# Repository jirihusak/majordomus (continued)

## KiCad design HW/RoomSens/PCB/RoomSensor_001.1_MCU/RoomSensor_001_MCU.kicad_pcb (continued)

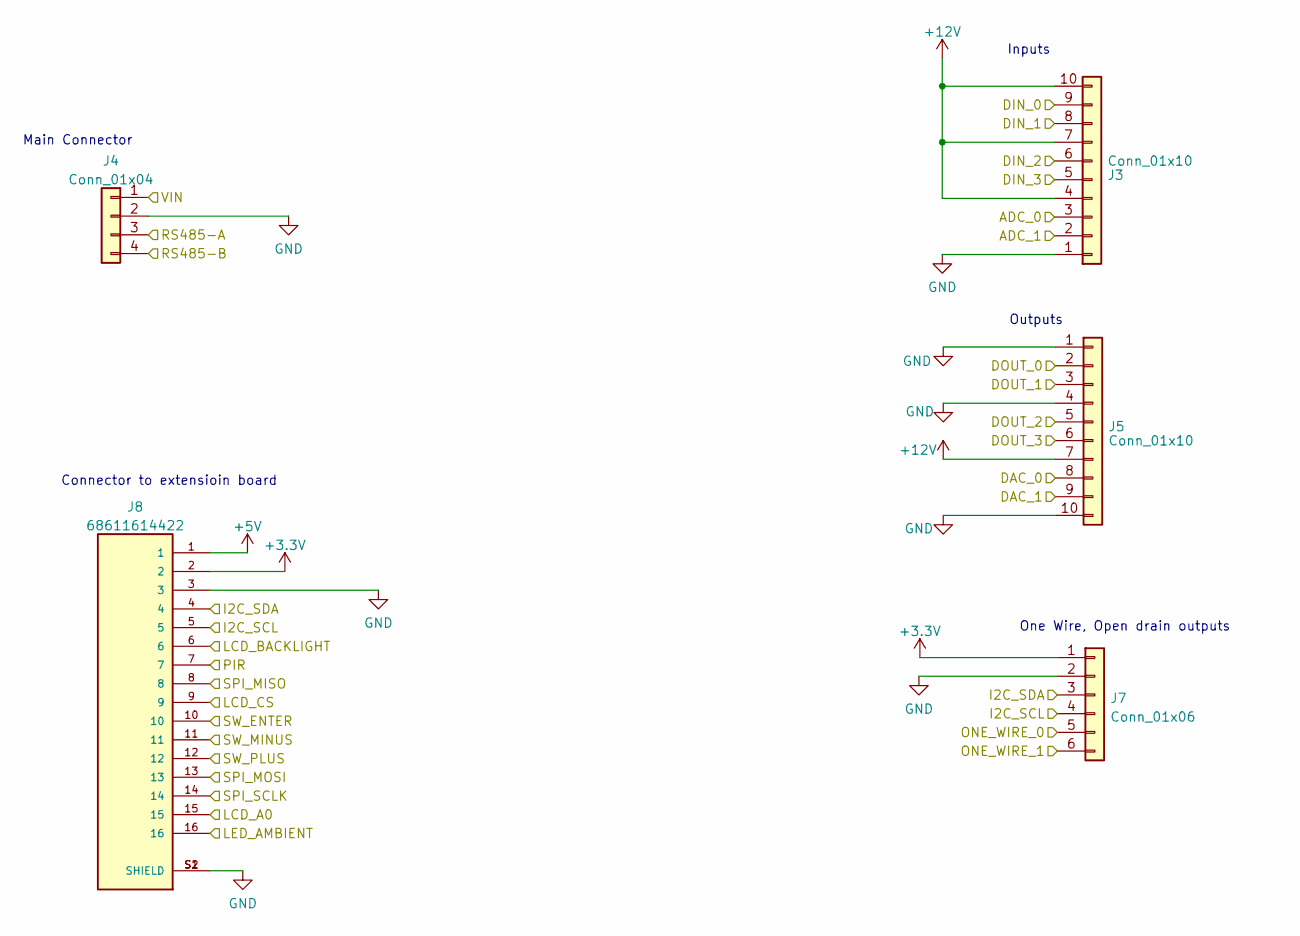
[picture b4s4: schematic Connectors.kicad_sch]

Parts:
J3, J5: Conn_01x10; PhoenixContact_MCV_1,5_10-G-3.5_1x10_P3.50mm_Vertical
J4: Conn_01x04; PhoenixContact_MSTBVA_2,5_4-G_1x04_P5.00mm_Vertical
J7: Conn_01x06; PinSocket_2x03_P2.54mm_Vertical
J8: 68611614422; WURTH_68611614422; PARTREV 001.006

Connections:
+3.3V: J7.1, J8.2; also elsewhere on the board
+5V: J8.1; also elsewhere on the board
+12V: J3.4, J3.7, J3.10, J5.7; also elsewhere on the board
/Connectors/ADC_0: J3.3; also elsewhere on the board
/Connectors/ADC_1: J3.2; also elsewhere on the board
/Connectors/DAC_0: J5.8; also elsewhere on the board
/Connectors/DAC_1: J5.9; also elsewhere on the board
/Connectors/DIN_0: J3.9; also elsewhere on the board
/Connectors/DIN_1: J3.8; also elsewhere on the board
/Connectors/DIN_2: J3.6; also elsewhere on the board
/Connectors/DIN_3: J3.5; also elsewhere on the board
/Connectors/DOUT_0: J5.2; also elsewhere on the board
/Connectors/DOUT_1: J5.3; also elsewhere on the board
/Connectors/DOUT_2: J5.5; also elsewhere on the board
/Connectors/DOUT_3: J5.6; also elsewhere on the board
/Connectors/I2C_SCL: J7.4, J8.5; also elsewhere on the board
/Connectors/I2C_SDA: J7.3, J8.4; also elsewhere on the board
/Connectors/LCD_A0: J8.15; also elsewhere on the board
/Connectors/LCD_BACKLIGHT: J8.6; also elsewhere on the board
/Connectors/LCD_CS: J8.9; also elsewhere on the board
/Connectors/LED_AMBIENT: J8.16; also elsewhere on the board
/Connectors/ONE_WIRE_0: J7.5; also elsewhere on the board
/Connectors/ONE_WIRE_1: J7.6; also elsewhere on the board
/Connectors/PIR: J8.7; also elsewhere on the board
/Connectors/RS485-A: J4.3; also elsewhere on the board
/Connectors/RS485-B: J4.4; also elsewhere on the board
/Connectors/SPI_MISO: J8.8; also elsewhere on the board
/Connectors/SPI_MOSI: J8.13; also elsewhere on the board
/Connectors/SPI_SCLK: J8.14; also elsewhere on the board
/Connectors/SW_ENTER: J8.10; also elsewhere on the board
/Connectors/SW_MINUS: J8.11; also elsewhere on the board
/Connectors/SW_PLUS: J8.12; also elsewhere on the board
/Connectors/VIN: J4.1; also elsewhere on the board
GND: J3.1, J4.2, J5.1, J5.4, J5.10, J7.2, J8.3, J8.S1 (SHIELD), J8.S2 (SHIELD); also elsewhere on the board

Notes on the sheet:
Connector to extensioin board
Inputs
Main Connector
One Wire, Open drain outputs
Outputs

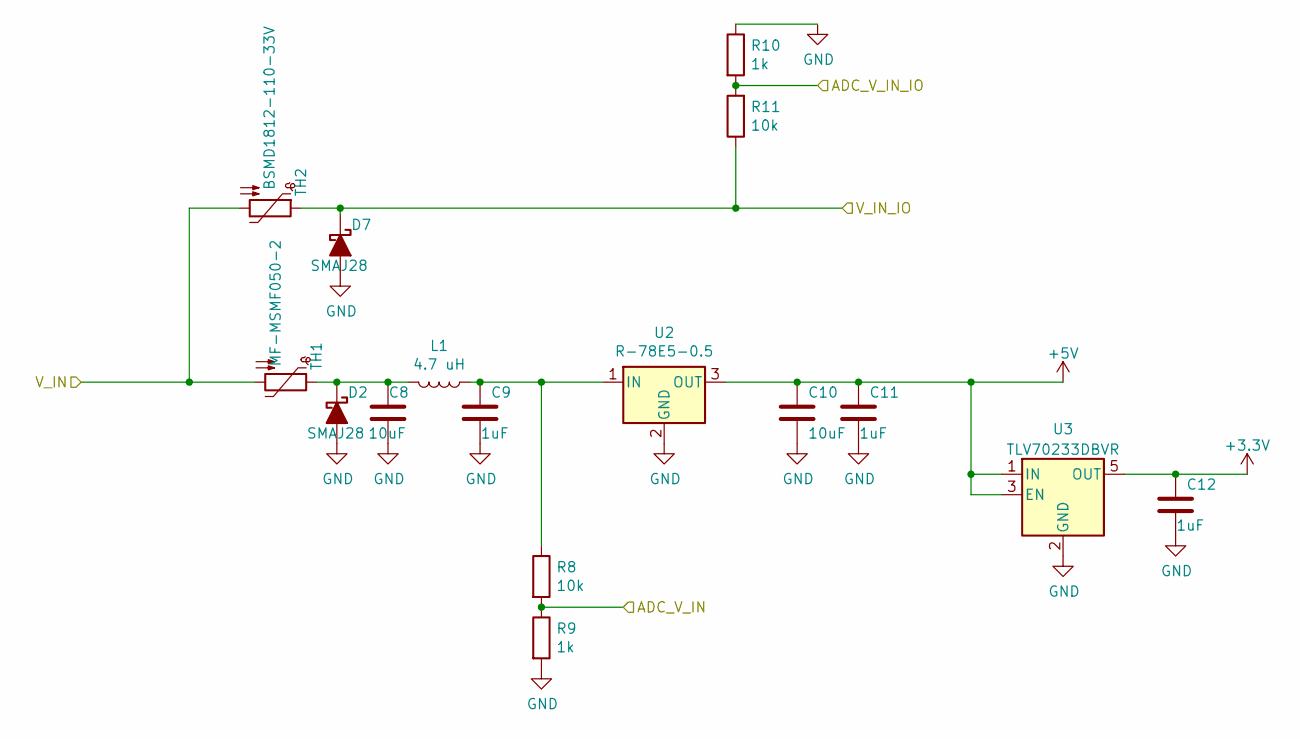
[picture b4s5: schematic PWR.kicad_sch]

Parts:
C8, C10: 10uF; C_1210_3225Metric
C9, C11, C12: 1uF; C_0805_2012Metric
D2, D7: SMAJ28; D_SMA
L1: 4.7 uH; L_0805_2012Metric
R8, R11: 10k; R_0805_2012Metric
R9, R10: 1k; R_0805_2012Metric
TH1: MF-MSMF050-2; Fuse_1812_4532Metric_Pad1.30x3.40mm_HandSolder
TH2: BSMD1812-110-33V; Fuse_1812_4532Metric_Pad1.30x3.40mm_HandSolder
U2: R-78E5-0.5; Converter_DCDC_RECOM_R-78E-0.5_THT
U3: TLV70233DBVR; SOT-23-5

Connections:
+3.3V: C12.1, U3.5 (OUT); also elsewhere on the board
+5V: C10.1, C11.1, U2.3 (OUT), U3.1 (IN), U3.3 (EN); also elsewhere on the board
+12V: D7.1 (K), R11.1, TH2.1; also elsewhere on the board
/Connectors/VIN: TH1.2, TH2.2; also elsewhere on the board
/MCU_PIC18/ADC_V_IN: R8.2, R9.1; also elsewhere on the board
/MCU_PIC18/ADC_V_IN_IO: R10.2, R11.2; also elsewhere on the board
GND: C8.2, C9.2, C10.2, C11.2, C12.2, D2.2 (A), D7.2 (A), R9.2, R10.1, U2.2 (GND), U3.2 (GND); also elsewhere on the board
unnamed: C8.1, D2.1 (K), L1.2, TH1.1
unnamed: C9.1, L1.1, R8.1, U2.1 (IN)

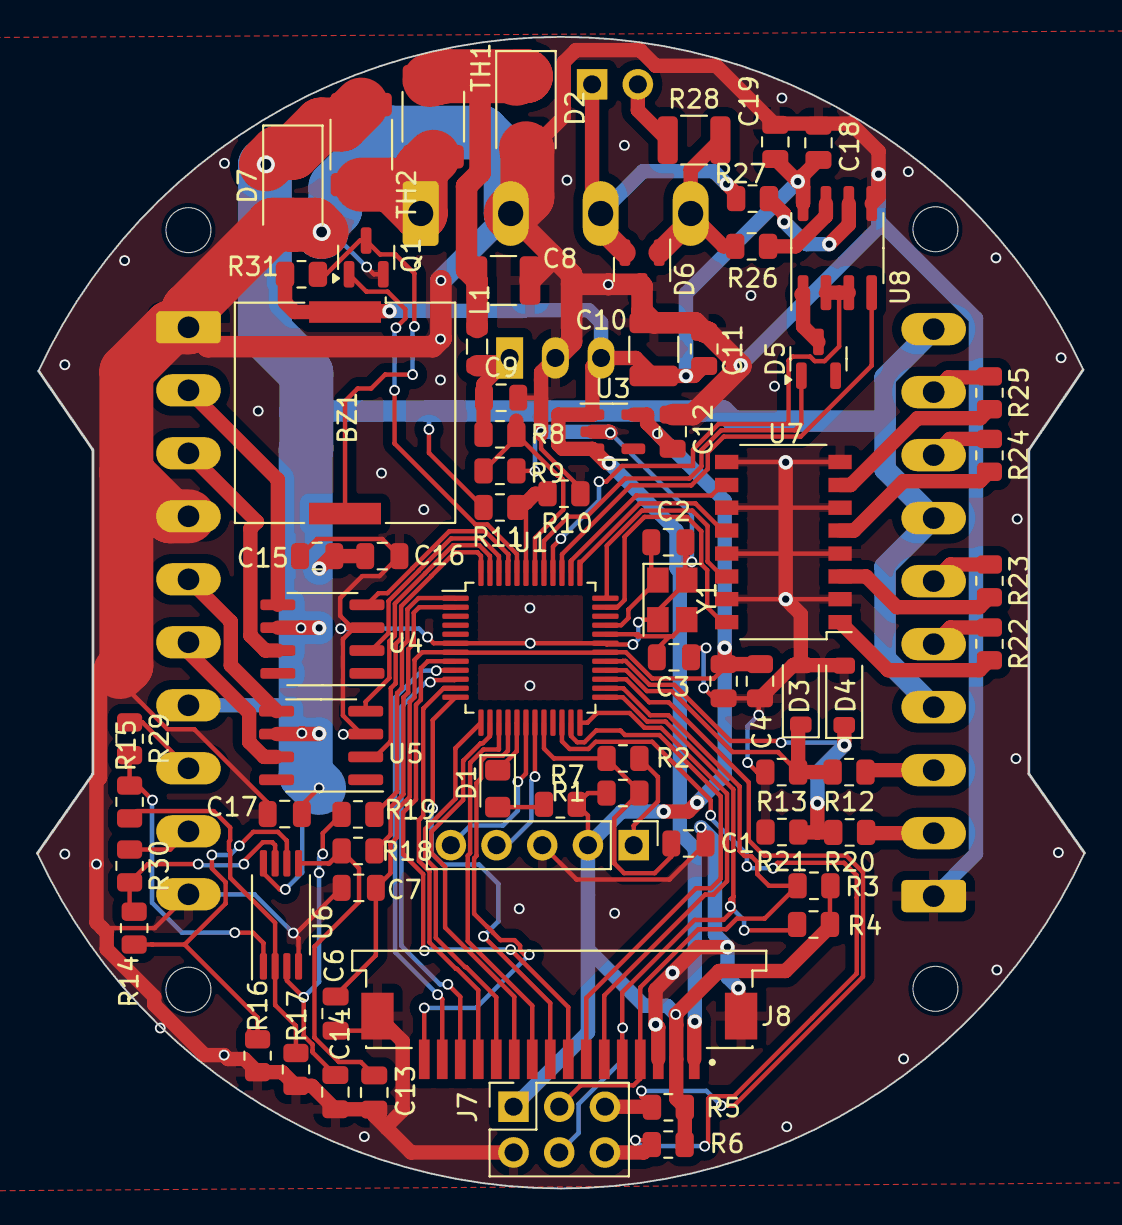
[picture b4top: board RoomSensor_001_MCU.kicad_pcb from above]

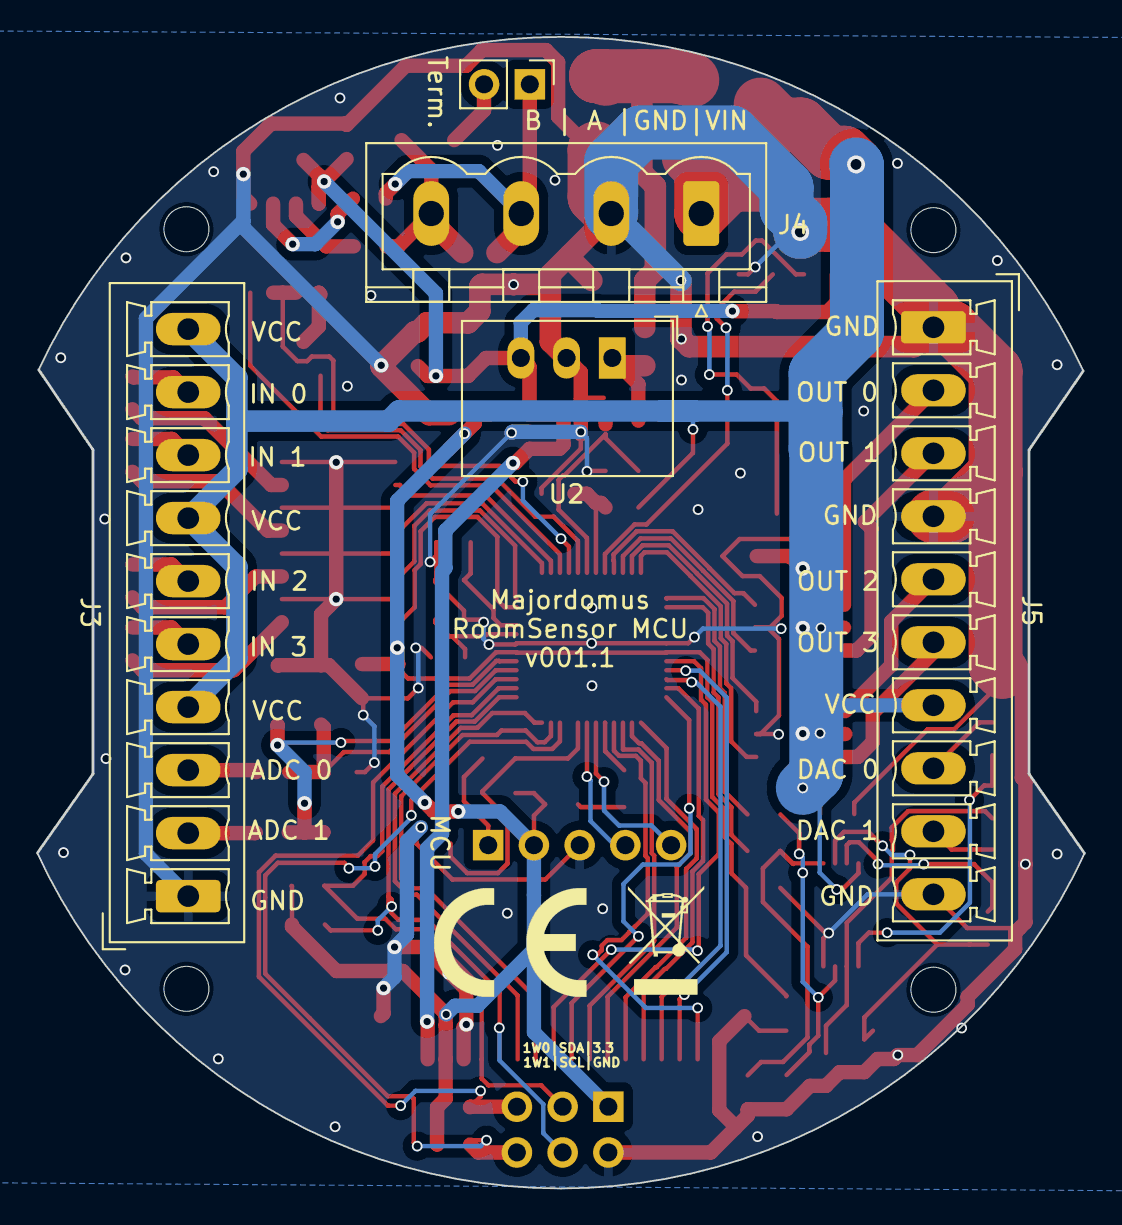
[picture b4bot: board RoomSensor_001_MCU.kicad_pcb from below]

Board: 2 copper layers, 58.2 x 63.9 mm, 82 parts (5 on the bottom side), 77 nets.

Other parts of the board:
 : MountingHole_2.5mm
 #2,  #3,  #4: MountingHole_2.5mm
MCU: CONN_DEBUG; PinHeader_1x05_P2.54mm_Vertical
Term.: Jumper; PinHeader_1x02_P2.54mm_Vertical

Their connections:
+3.3V: MCU.2; also elsewhere on the board
/Connectors/RS485-A: Term..1; also elsewhere on the board
GND: MCU.3; also elsewhere on the board
ICSPCLK: MCU.5; also elsewhere on the board
ICSPDAT: MCU.4; also elsewhere on the board
unnamed 62: MCU.1; also elsewhere on the board
unnamed 63: Term..2; also elsewhere on the board

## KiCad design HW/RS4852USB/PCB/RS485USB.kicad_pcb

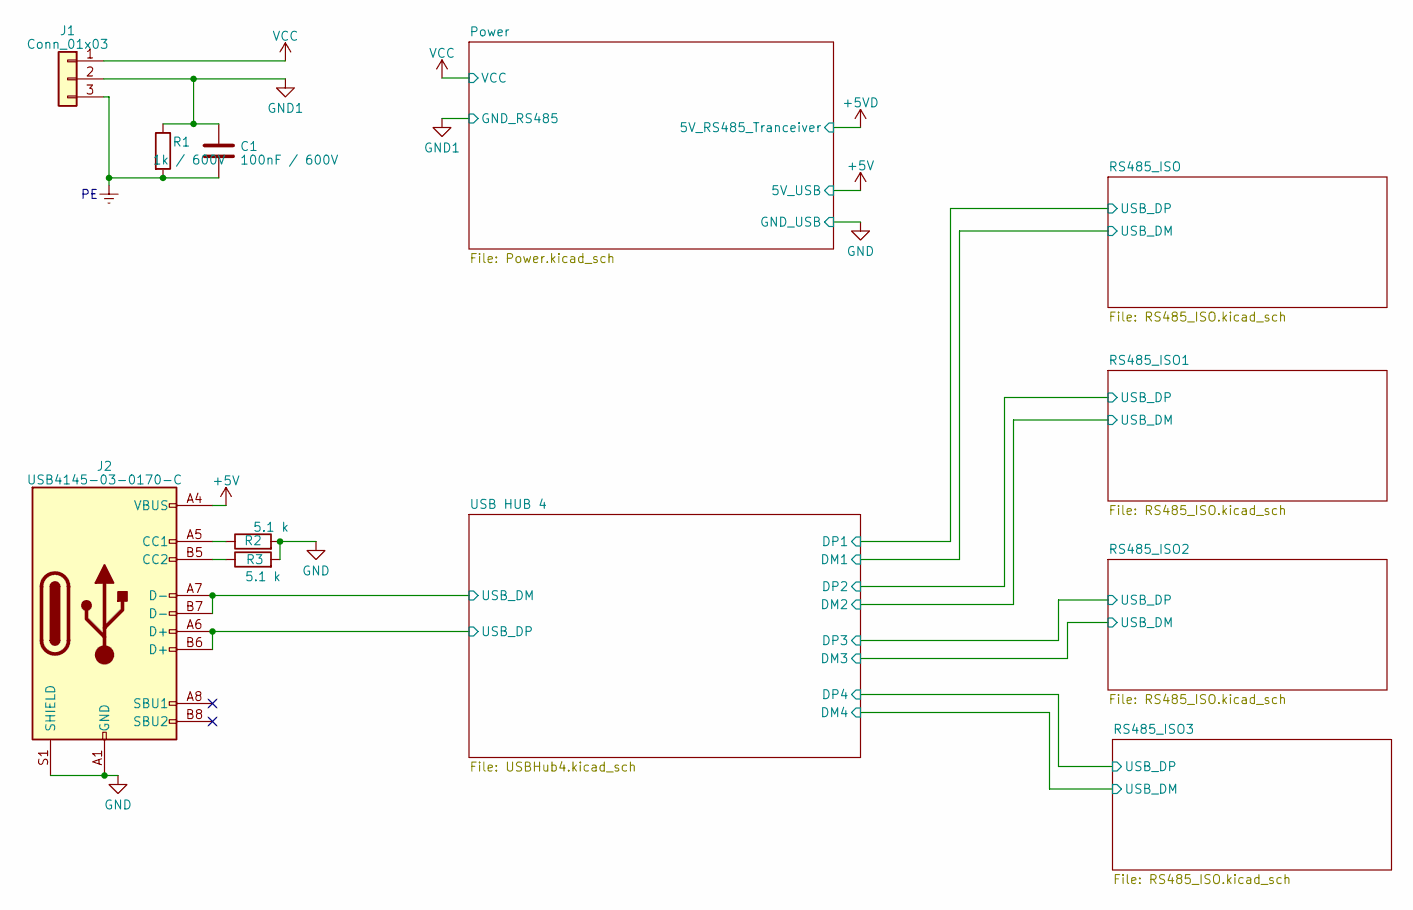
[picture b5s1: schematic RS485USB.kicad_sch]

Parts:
C1: 100nF / 600V; C_1812_4532Metric_Pad1.57x3.40mm_HandSolder
J1: Conn_01x03; PhoenixContact_MSTBV_2,5_3-GF_1x03_P5.00mm_Vertical_Threade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
J2: USB4145-03-0170-C; GCT_USB4145
R1: 1k / 600V; R_Axial_DIN0309_L9.0mm_D3.2mm_P12.70mm_Horizontal
R2, R3: 5.1 k; R_0805_2012Metric

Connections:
+5V: J2.A4 (VBUS), J2.A9 (VBUS), J2.B4 (VBUS), J2.B9 (VBUS); also elsewhere on the board
/USB HUB 4/USB_DM: J2.A7 (D-), J2.B7 (D-); also elsewhere on the board
/USB HUB 4/USB_DP: J2.A6 (D+), J2.B6 (D+); also elsewhere on the board
Earth: C1.2, J1.3, R1.2
GND: J2.A1 (GND), J2.A12 (GND), J2.B1 (GND), J2.B12 (GND), J2.S1 (SHIELD), R2.2, R3.2; also elsewhere on the board
GND1: C1.1, J1.2, R1.1; also elsewhere on the board
unnamed: J2.A5 (CC1), R2.1
unnamed: J2.B5 (CC2), R3.1
VCC: J1.1; also elsewhere on the board

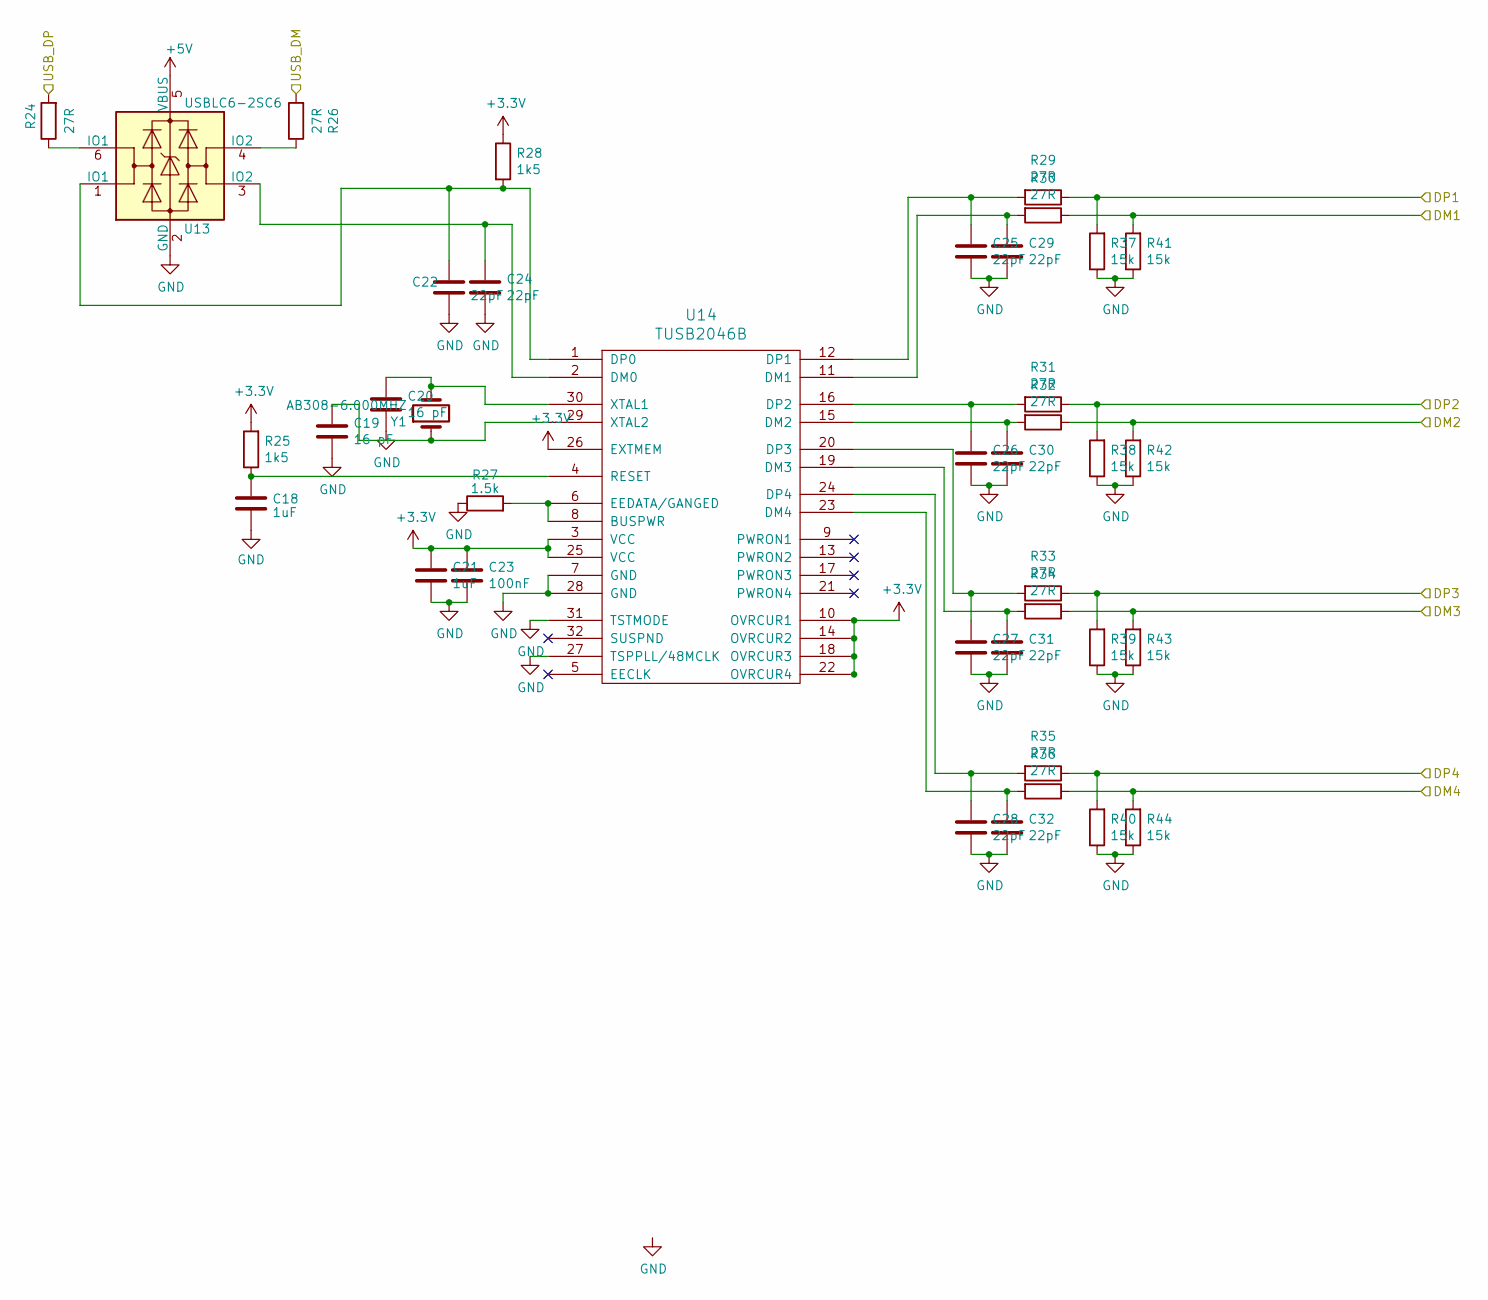
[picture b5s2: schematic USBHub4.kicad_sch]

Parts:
C18, C21: 1uF; C_0805_2012Metric
C19, C20: 16 pF; C_0805_2012Metric
C22, C24, C25, C26, C27, C28, C29, C30, C31, C32: 22pF; C_0805_2012Metric
C23: 100nF; C_0805_2012Metric
R24, R26, R29, R30, R31, R32, R33, R34, R35, R36: 27R; R_0805_2012Metric
R25, R28: 1k5; R_0805_2012Metric
R27: 1.5k; R_0805_2012Metric
R37, R38, R39, R40, R41, R42, R43, R44: 15k; R_0805_2012Metric
U13: USBLC6-2SC6; SOT-23-6
U14: TUSB2046B; LQFP-32_7x7mm_P0.8mm
Y1: AB308-6.000MHZ; Crystal_C38-LF_D3.0mm_L8.0mm_Horizontal

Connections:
+5V: U13.5 (VBUS); also elsewhere on the board
/RS485_ISO1/USB_DM: R32.1, R42.2; also elsewhere on the board
/RS485_ISO1/USB_DP: R31.1, R38.2; also elsewhere on the board
/RS485_ISO2/USB_DM: R34.1, R43.2; also elsewhere on the board
/RS485_ISO2/USB_DP: R33.1, R39.2; also elsewhere on the board
/RS485_ISO3/USB_DM: R36.1, R44.2; also elsewhere on the board
/RS485_ISO3/USB_DP: R35.1, R40.2; also elsewhere on the board
/RS485_ISO/USB_DM: R30.1, R41.2; also elsewhere on the board
/RS485_ISO/USB_DP: R29.1, R37.2; also elsewhere on the board
/USB HUB 4/USB_DM: R26.2; also elsewhere on the board
/USB HUB 4/USB_DP: R24.2; also elsewhere on the board
GND: C18.2, C19.2, C20.2, C21.2, C22.2, C23.2, C24.2, C25.2, C26.2, C27.2, C28.2, C29.2, C30.2, C31.2, C32.2, R27.1, R37.1, R38.1, R39.1, R40.1, R41.1, R42.1, R43.1, R44.1, U13.2 (GND), U14.7 (GND), U14.27 (TSPPLL/48MCLK), U14.28 (GND), U14.31 (TSTMODE); also elsewhere on the board
unnamed: R24.1, U13.6 (IO1)
unnamed: R26.1, U13.4 (IO2)
unnamed: R27.2, U14.6 (EEDATA/GANGED), U14.8 (BUSPWR)
unnamed: C24.1, U13.3 (IO2), U14.2 (DM0)
unnamed: C29.1, R30.2, U14.11 (DM1)
unnamed: C30.1, R32.2, U14.15 (DM2)
unnamed: C31.1, R34.2, U14.19 (DM3)
unnamed: C32.1, R36.2, U14.23 (DM4)
unnamed: C22.1, R28.2, U13.1 (IO1), U14.1 (DP0)
unnamed: C25.1, R29.2, U14.12 (DP1)
unnamed: C26.1, R31.2, U14.16 (DP2)
unnamed: C27.1, R33.2, U14.20 (DP3)
unnamed: C28.1, R35.2, U14.24 (DP4)
unnamed: C18.1, R25.1, U14.4 (RESET)
unnamed: C20.1, U14.30 (XTAL1), Y1.2
unnamed: C19.1, U14.29 (XTAL2), Y1.1

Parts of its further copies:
C8: 100nF; C_0805_2012Metric

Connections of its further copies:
+5VD: C8.1; also elsewhere on the board
GND1: C8.2; also elsewhere on the board

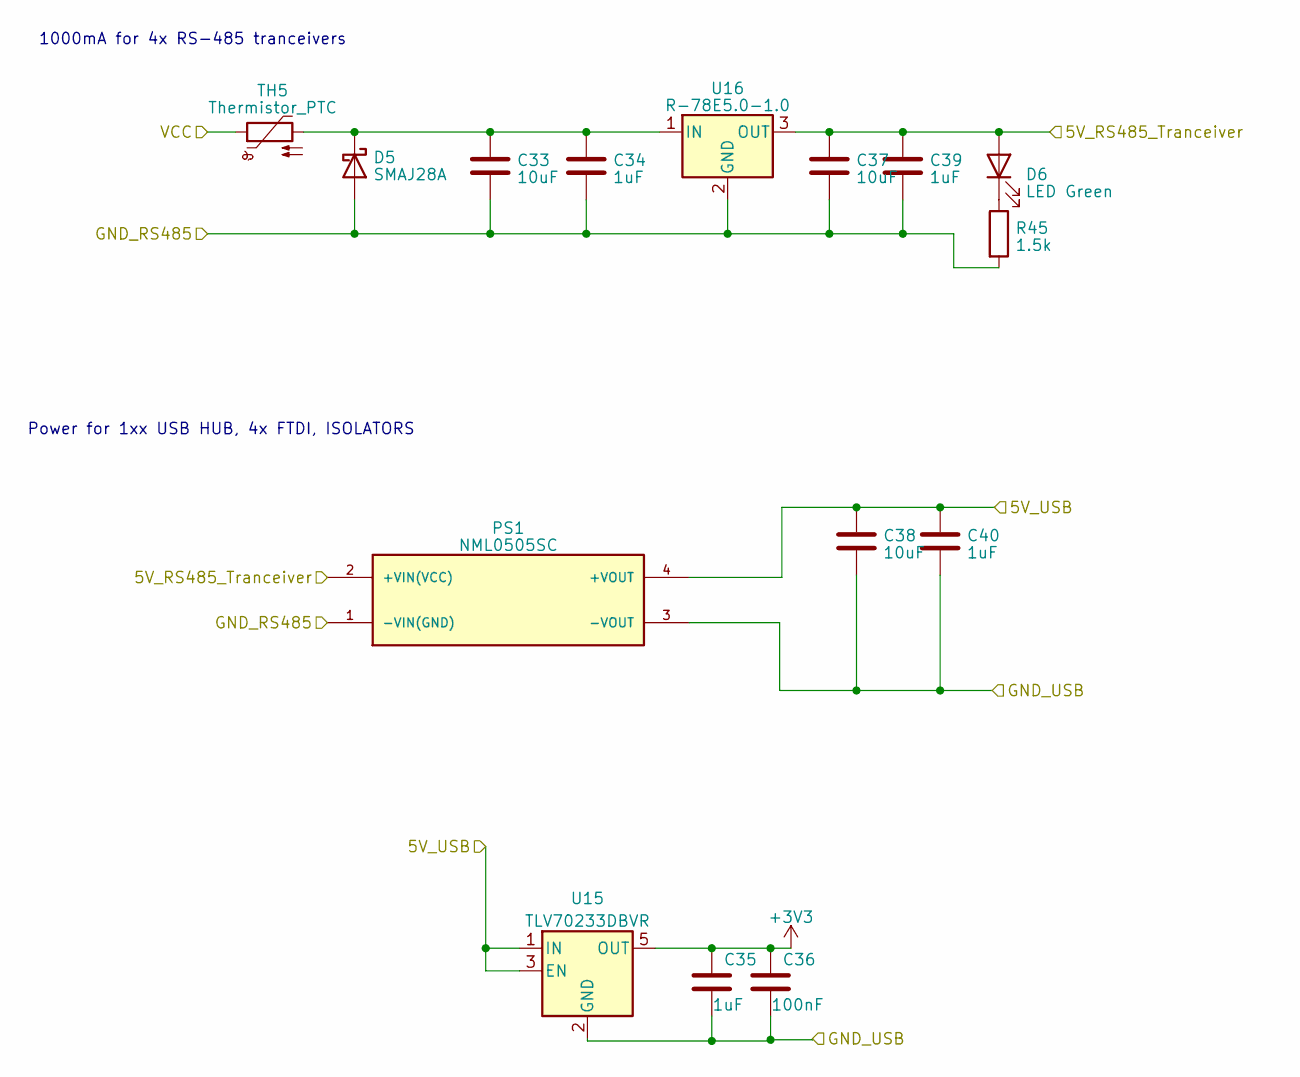
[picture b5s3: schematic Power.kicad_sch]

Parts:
C33, C37, C38: 10uF; C_1210_3225Metric
C34, C35, C39, C40: 1uF; C_0805_2012Metric
C36: 100nF; C_0805_2012Metric
D5: SMAJ28A; D_SMA
D6: LED Green; LED_0805_2012Metric
PS1: NML0505SC; NML0505S; PARTREV April 19, 2021
R45: 1.5k; R_0805_2012Metric
TH5: Thermistor_PTC; R_1812_4532Metric
U15: TLV70233DBVR; SOT-23-5
U16: R-78E5.0-1.0; Converter_DCDC_RECOM_R-78E-0.5_THT

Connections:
+5V: C38.1, C40.1, PS1.4 (+VOUT), U15.1 (IN), U15.3 (EN); also elsewhere on the board
+5VD: C37.1, C39.1, D6.2 (A), PS1.2 (+VIN(VCC)), U16.3 (OUT); also elsewhere on the board
GND: C35.2, C36.2, C38.2, C40.2, PS1.3 (-VOUT), U15.2 (GND); also elsewhere on the board
GND1: C33.2, C34.2, C37.2, C39.2, D5.2 (A), PS1.1 (-VIN(GND)), R45.2, U16.2 (GND); also elsewhere on the board
unnamed: C33.1, C34.1, D5.1 (K), TH5.2, U16.1 (IN)
unnamed: D6.1 (K), R45.1
VCC: TH5.1; also elsewhere on the board

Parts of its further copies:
C12: 100nF; C_0805_2012Metric

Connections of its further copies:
+5VD: C12.1; also elsewhere on the board
GND1: C12.2; also elsewhere on the board

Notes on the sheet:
1000mA for 4x RS-485 tranceivers
Power for 1xx USB HUB, 4x FTDI, ISOLATORS

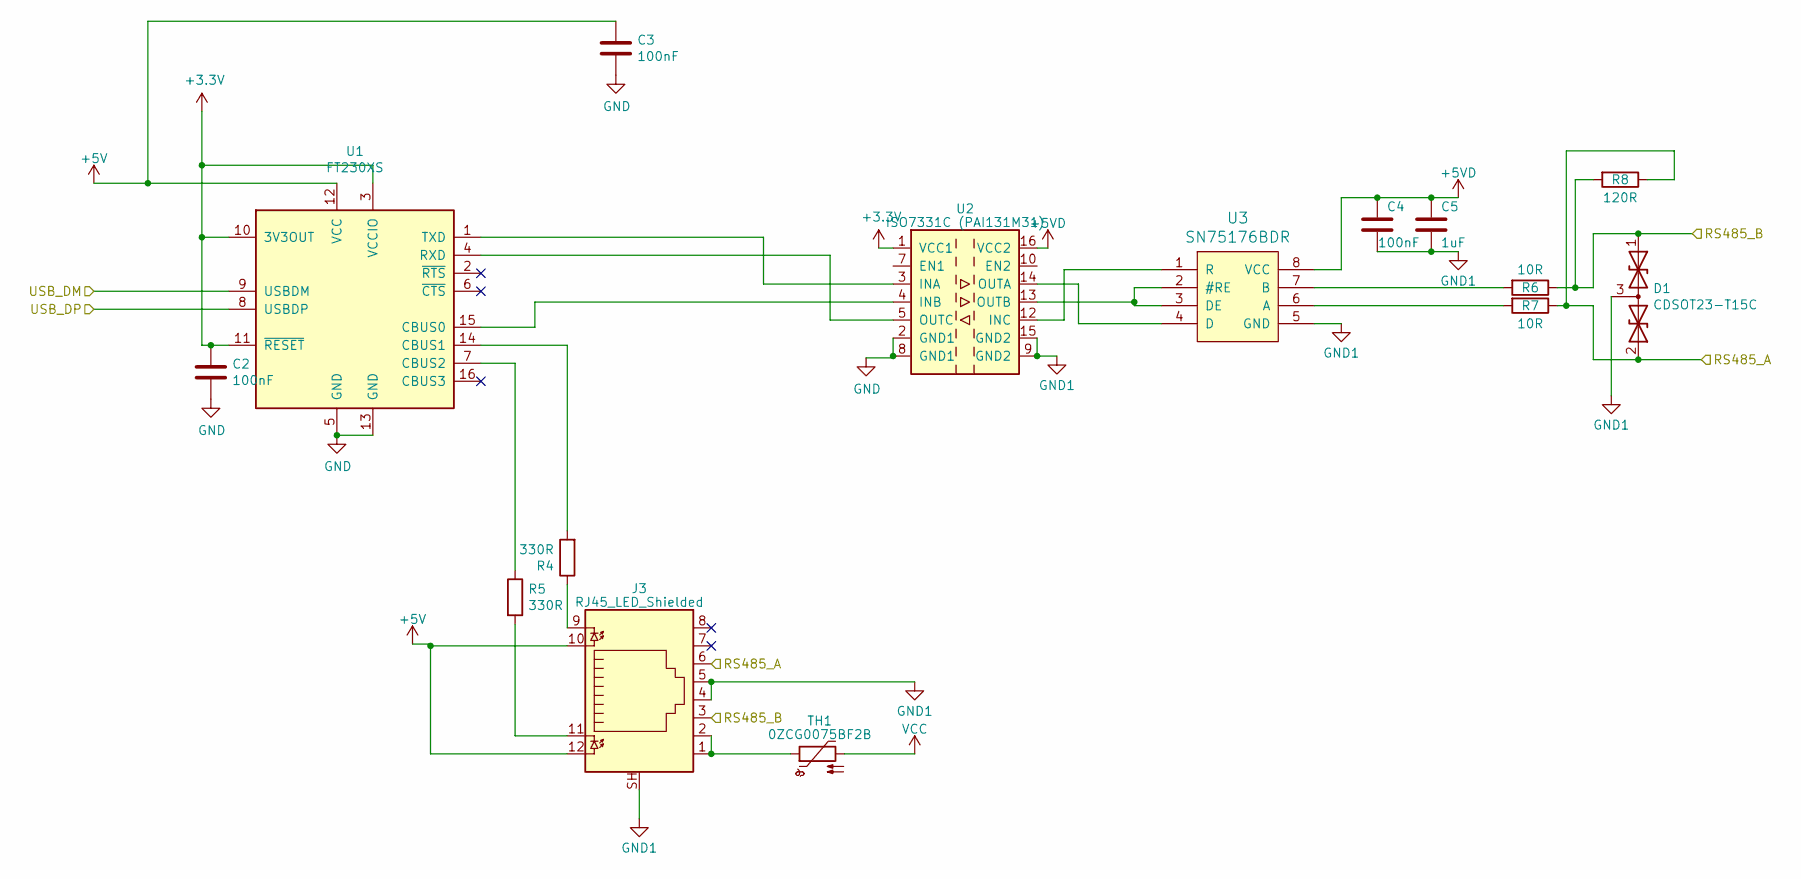
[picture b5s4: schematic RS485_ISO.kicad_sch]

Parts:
C2, C3, C4: 100nF; C_0805_2012Metric
C5: 1uF; C_0805_2012Metric
D1: CDSOT23-T15C; SOT-23
J3: RJ45_LED_Shielded; RJ45_Amphenol_RJHSE3384
R4, R5: 330R; R_0805_2012Metric
R6, R7: 10R; R_0805_2012Metric
R8: 120R; R_1210_3225Metric
TH1: 0ZCG0075BF2B; R_1812_4532Metric
U1: FT230XS; SSOP-16_3.9x4.9mm_P0.635mm
U2: ISO7331C (PAI131M31); SO-16_3.9x9.9mm_P1.27mm
U3: SN75176BDR; SOIC-8_3.9x4.9mm_P1.27mm

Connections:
+5V: C3.1, J3.10, J3.12, U1.12 (VCC); also elsewhere on the board
+5VD: C4.1, C5.1, U2.16 (VCC2), U3.8 (VCC); also elsewhere on the board
/RS485_ISO/RS485_A: D1.2 (A2), J3.6, R7.1, R8.1
/RS485_ISO/RS485_B: D1.1 (A1), J3.3, R6.1, R8.2
/RS485_ISO/USB_DM: U1.9 (USBDM); also elsewhere on the board
/RS485_ISO/USB_DP: U1.8 (USBDP); also elsewhere on the board
GND: C2.2, C3.2, U1.5 (GND), U1.13 (GND), U2.2 (GND1), U2.8 (GND1); also elsewhere on the board
GND1: C4.2, C5.2, D1.3 (common), J3.4, J3.5, J3.SH, U2.9 (GND2), U2.15 (GND2), U3.5 (GND); also elsewhere on the board
unnamed: J3.1, J3.2, TH1.1
unnamed: J3.9, R4.1
unnamed: J3.11, R5.2
unnamed: U1.15 (CBUS0), U2.4 (INB)
unnamed: R4.2, U1.14 (CBUS1)
unnamed: R5.1, U1.7 (CBUS2)
unnamed: U1.4 (RXD), U2.5 (OUTC)
unnamed: U1.1 (TXD), U2.3 (INA)
unnamed: U2.12 (INC), U3.1 (R)
unnamed: U2.14 (OUTA), U3.4 (D)
unnamed: U2.13 (OUTB), U3.2 (#RE), U3.3 (DE)
unnamed: R7.2, U3.6 (A)
unnamed: R6.2, U3.7 (B)
VCC: TH1.2; also elsewhere on the board

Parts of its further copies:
C6, C7, C8, C10, C11, C12, C14, C15, C16: 100nF; C_0805_2012Metric
C9, C13, C17: 1uF; C_0805_2012Metric
D2, D3, D4: CDSOT23-T15C; SOT-23
J4, J5, J6: RJ45_LED_Shielded; RJ45_Amphenol_RJHSE3384
R9, R10, R14, R15, R19, R20: 330R; R_0805_2012Metric
R11, R12, R16, R17, R21, R22: 10R; R_0805_2012Metric
R13, R18, R23: 120R; R_1210_3225Metric
U4, U7, U10: FT230XS; SSOP-16_3.9x4.9mm_P0.635mm
U5, U11: ISO7331C (PAI131M31); SO-16_3.9x9.9mm_P1.27mm
U6, U9, U12: SN75176BDR; SOIC-8_3.9x4.9mm_P1.27mm

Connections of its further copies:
+5V: C7.1, C11.1, C15.1, J4.10, J4.12, J5.10, J5.12, J6.10, J6.12, U4.12 (VCC), U7.12 (VCC), U10.12 (VCC); also elsewhere on the board
+5VD: C8.1, C9.1, C12.1, C13.1, C16.1, C17.1, U5.16 (VCC2), U6.8 (VCC), U9.8 (VCC), U11.16 (VCC2), U12.8 (VCC); also elsewhere on the board
/RS485_ISO1/RS485_A: D2.2 (A2), J4.6, R12.1, R13.1
/RS485_ISO1/RS485_B: D2.1 (A1), J4.3, R11.1, R13.2
/RS485_ISO1/USB_DM: U4.9 (USBDM); also elsewhere on the board
/RS485_ISO1/USB_DP: U4.8 (USBDP); also elsewhere on the board
/RS485_ISO2/RS485_A: D3.2 (A2), J5.6, R17.1, R18.1
/RS485_ISO2/RS485_B: D3.1 (A1), J5.3, R16.1, R18.2
/RS485_ISO2/USB_DM: U7.9 (USBDM); also elsewhere on the board
/RS485_ISO2/USB_DP: U7.8 (USBDP); also elsewhere on the board
/RS485_ISO3/RS485_A: D4.2 (A2), J6.6, R22.1, R23.1
/RS485_ISO3/RS485_B: D4.1 (A1), J6.3, R21.1, R23.2
/RS485_ISO3/USB_DM: U10.9 (USBDM); also elsewhere on the board
/RS485_ISO3/USB_DP: U10.8 (USBDP); also elsewhere on the board
GND: C6.2, C7.2, C10.2, C11.2, C14.2, C15.2, U4.5 (GND), U4.13 (GND), U5.2 (GND1), U5.8 (GND1), U7.5 (GND), U7.13 (GND), U10.5 (GND), U10.13 (GND), U11.2 (GND1), U11.8 (GND1); also elsewhere on the board
GND1: C8.2, C9.2, C12.2, C13.2, C16.2, C17.2, D2.3 (common), D3.3 (common), D4.3 (common), J4.4, J4.5, J4.SH, J5.4, J5.5, J5.SH, J6.4, J6.5, J6.SH, U5.9 (GND2), U5.15 (GND2), U6.5 (GND), U9.5 (GND), U11.9 (GND2), U11.15 (GND2), U12.5 (GND); also elsewhere on the board
unnamed 30: J4.1, J4.2; also elsewhere on the board
unnamed: J4.9, R9.1
unnamed: J4.11, R10.2
unnamed 33: J5.1, J5.2; also elsewhere on the board
unnamed: J5.9, R14.1
unnamed: J5.11, R15.2
unnamed 36: J6.1, J6.2; also elsewhere on the board
unnamed: J6.9, R19.1
unnamed: J6.11, R20.2
unnamed: U4.15 (CBUS0), U5.4 (INB)
unnamed: R9.2, U4.14 (CBUS1)
unnamed: R10.1, U4.7 (CBUS2)
unnamed: U4.4 (RXD), U5.5 (OUTC)
unnamed: U4.1 (TXD), U5.3 (INA)
unnamed: U5.12 (INC), U6.1 (R)
unnamed: U5.14 (OUTA), U6.4 (D)
unnamed: U5.13 (OUTB), U6.2 (#RE), U6.3 (DE)
unnamed: R12.2, U6.6 (A)
unnamed: R11.2, U6.7 (B)
unnamed 61: U7.15 (CBUS0); also elsewhere on the board
unnamed: R14.2, U7.14 (CBUS1)
unnamed: R15.1, U7.7 (CBUS2)
unnamed 64: U7.4 (RXD); also elsewhere on the board
unnamed 65: U7.1 (TXD); also elsewhere on the board
unnamed 66: U9.1 (R); also elsewhere on the board
unnamed 67: U9.4 (D); also elsewhere on the board
unnamed 68: U9.2 (#RE), U9.3 (DE); also elsewhere on the board
unnamed: R17.2, U9.6 (A)
unnamed: R16.2, U9.7 (B)
unnamed: U10.15 (CBUS0), U11.4 (INB)
unnamed: R19.2, U10.14 (CBUS1)
unnamed: R20.1, U10.7 (CBUS2)
unnamed: U10.4 (RXD), U11.5 (OUTC)
unnamed: U10.1 (TXD), U11.3 (INA)
unnamed: U11.12 (INC), U12.1 (R)
unnamed: U11.14 (OUTA), U12.4 (D)
unnamed: U11.13 (OUTB), U12.2 (#RE), U12.3 (DE)
unnamed: R22.2, U12.6 (A)
unnamed: R21.2, U12.7 (B)

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
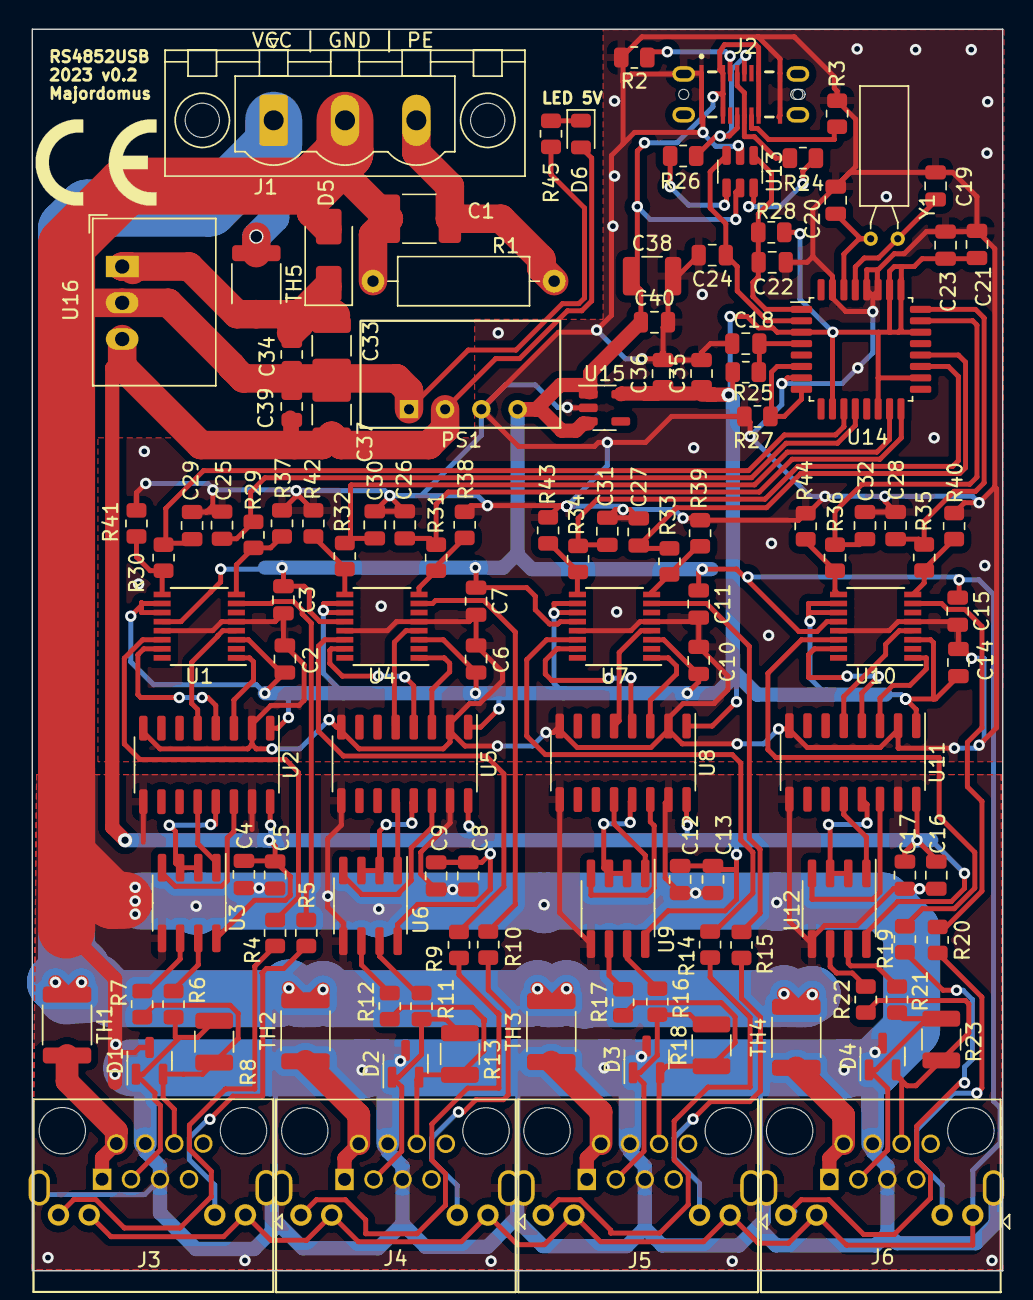
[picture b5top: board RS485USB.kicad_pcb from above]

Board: 2 copper layers, 68.0 x 87.0 mm, 120 parts (0 on the bottom side), 97 nets.

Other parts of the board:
TH2, TH3, TH4: Thermistor_PTC; R_1812_4532Metric
U8: ISO7331C (PAI131M31); SO-16_3.9x9.9mm_P1.27mm

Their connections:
+5VD: U8.16 (VCC2); also elsewhere on the board
GND: U8.2 (GND1), U8.8 (GND1); also elsewhere on the board
GND1: U8.9 (GND2), U8.15 (GND2); also elsewhere on the board
unnamed 30: TH2.1; also elsewhere on the board
unnamed 33: TH3.1; also elsewhere on the board
unnamed 36: TH4.1; also elsewhere on the board
unnamed 61: U8.4 (INB); also elsewhere on the board
unnamed 64: U8.5 (OUTC); also elsewhere on the board
unnamed 65: U8.3 (INA); also elsewhere on the board
unnamed 66: U8.12 (INC); also elsewhere on the board
unnamed 67: U8.14 (OUTA); also elsewhere on the board
unnamed 68: U8.13 (OUTB); also elsewhere on the board
VCC: TH2.2, TH3.2, TH4.2; also elsewhere on the board

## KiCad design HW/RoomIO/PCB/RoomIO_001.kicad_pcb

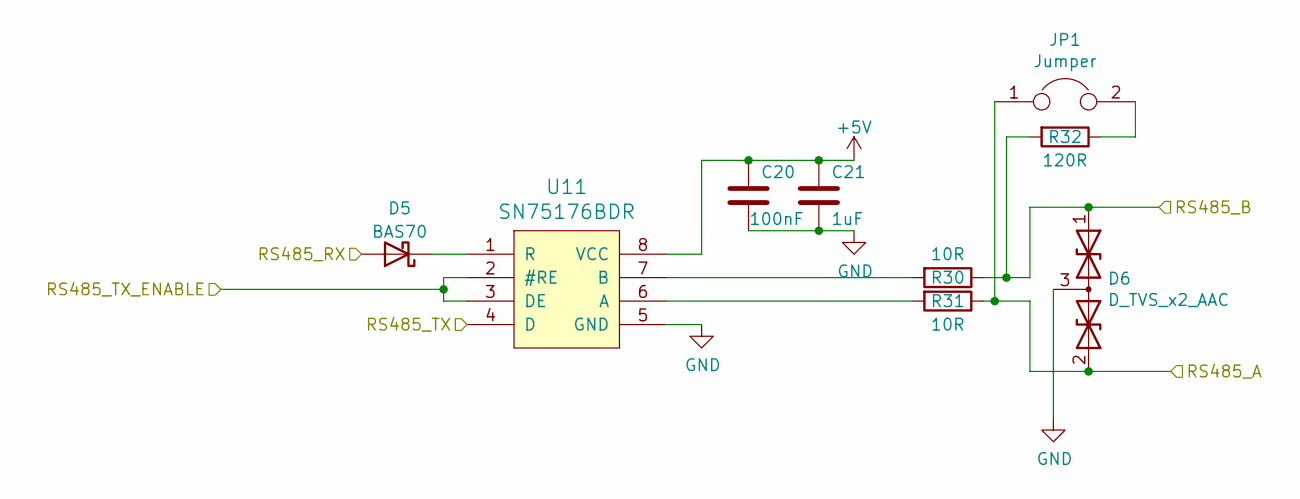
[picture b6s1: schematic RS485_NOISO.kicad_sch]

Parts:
C20: 100nF; C_0805_2012Metric
C21: 1uF; C_0805_2012Metric
D5: BAS70; SOT-23
D6: D_TVS_x2_AAC; SOT-23
JP1: Jumper; PinHeader_1x02_P2.54mm_Vertical
R30, R31: 10R; R_0805_2012Metric
R32: 120R; R_1210_3225Metric
U11: SN75176BDR; SOIC-8_3.9x4.9mm_P1.27mm

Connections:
+5V: C20.1, C21.1, U11.8 (VCC); also elsewhere on the board
/Connectors/RS485-A: D6.2 (A2), JP1.1, R31.1; also elsewhere on the board
/Connectors/RS485-B: D6.1 (A1), R30.1, R32.2; also elsewhere on the board
/MCU_PIC18/RS485_RX: U11.4 (D); also elsewhere on the board
/MCU_PIC18/RS485_TX: D5.2 (A); also elsewhere on the board
/MCU_PIC18/RS485_TX_ENABLE: U11.2 (#RE), U11.3 (DE); also elsewhere on the board
GND: C20.2, C21.2, D6.3 (common), U11.5 (GND); also elsewhere on the board
unnamed: D5.1 (K), U11.1 (R)
unnamed 64: JP1.2, R32.1; also elsewhere on the board
unnamed: R31.2, U11.6 (A)
unnamed: R30.2, U11.7 (B)
